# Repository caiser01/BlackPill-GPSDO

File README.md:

# BlackPill GPSDO
A custom PCB design for use with AndrewBCN's STM32-GPSDO project (https://github.com/AndrewBCN/STM32-GPSDO).

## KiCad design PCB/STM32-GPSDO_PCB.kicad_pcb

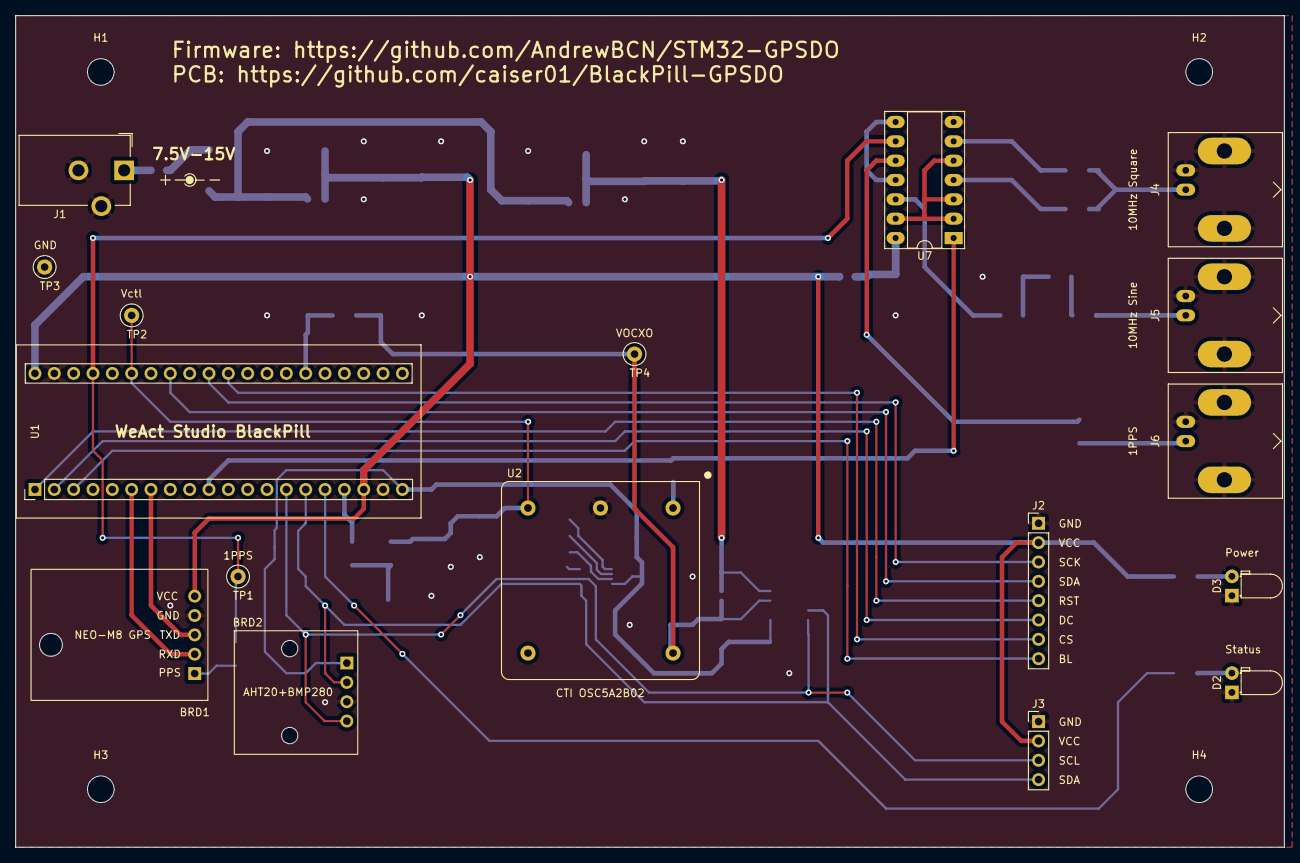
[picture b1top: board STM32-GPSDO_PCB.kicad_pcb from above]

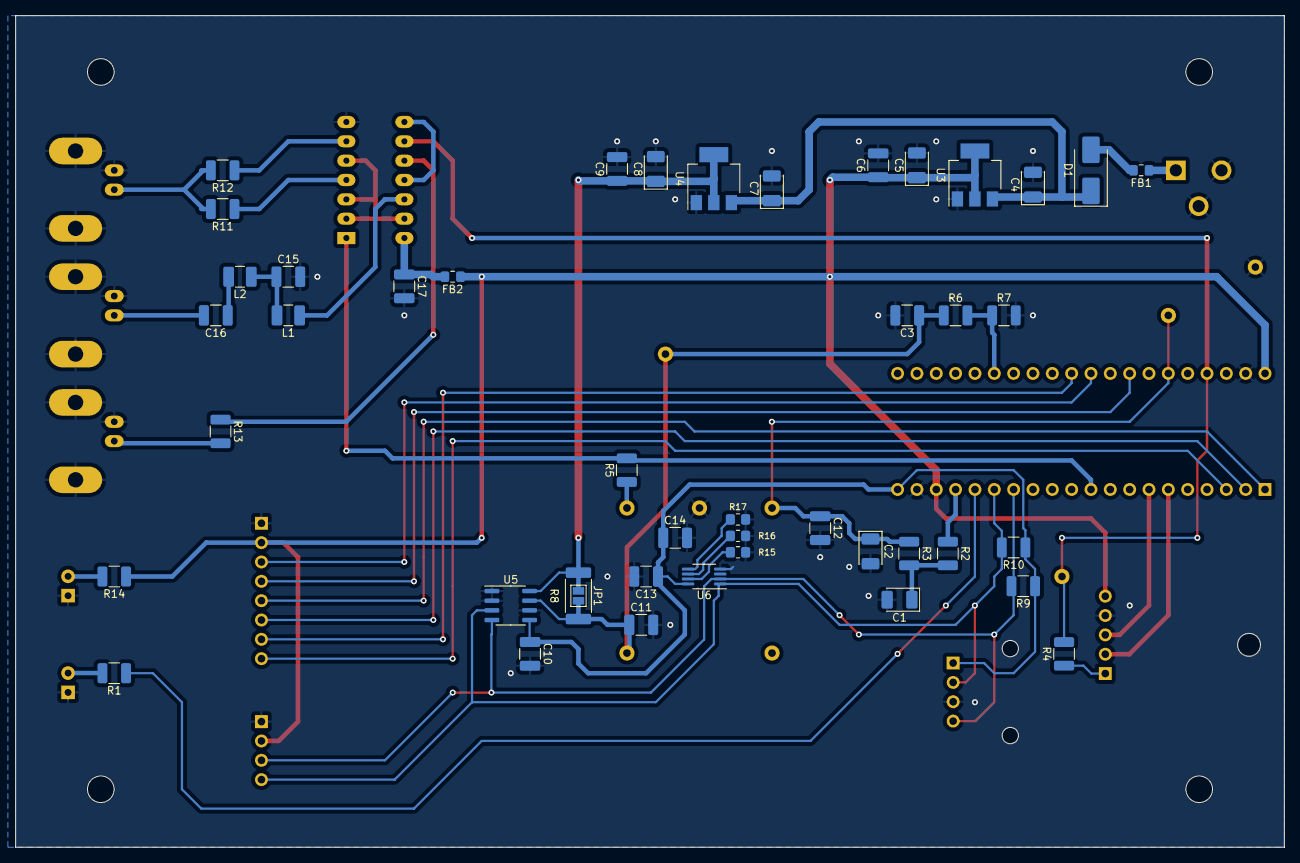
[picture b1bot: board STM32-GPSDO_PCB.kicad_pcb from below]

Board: 2 copper layers, 166.6 x 109.2 mm, 65 parts (44 on the bottom side), 44 nets.

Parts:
BRD1: NEO-M8N_GPS_Module; PCB_modules_GPS_NEO-M8N_PCB
BRD2: AHT20+BMP280_Module; PCB_modules_AHT20_BMP280_PCB
C1, C2: 10μF / 16V; CP_EIA-3528-15_AVX-H_Pad1.50x2.35mm_HandSolder
C3, C6, C9, C10, C11, C12, C13, C16, C17: 0.1μF; C_1210_3225Metric_Pad1.33x2.70mm_HandSolder
C4, C5, C7, C8: 10μF; CP_EIA-3528-12_Kemet-T_Pad1.50x2.35mm_HandSolder
C14: 10μF; C_1210_3225Metric_Pad1.33x2.70mm_HandSolder
C15: 47pF; C_1210_3225Metric_Pad1.33x2.70mm_HandSolder
D1: S2M-13-F; D_SMB_Handsoldering
D2: Status; LED_D3.0mm_Horizontal_O1.27mm_Z2.0mm
D3: Power; LED_D3.0mm_Horizontal_O1.27mm_Z2.0mm
FB1, FB2: MH2029-300Y; L_0805_2012Metric_Pad1.15x1.40mm_HandSolder
H1, H2, H3, H4: MountingHole; MountingHole_3.5mm
J1: Barrel_Jack_Switch; BarrelJack_CUI_PJ-102AH_Horizontal
J2: LCD_SPI; PinHeader_1x08_P2.54mm_Vertical
J3: LCD_I2C; PinHeader_1x04_P2.54mm_Vertical
J4, J5, J6: Conn_Coaxial; BNC_Amphenol_B6252HB-NPP3G-50_Horizontal
JP1: N.O.; SolderJumper-2_P1.3mm_Open_Pad1.0x1.5mm
L1, L2: L_Ferrite 10μH; L_1210_3225Metric_Pad1.42x2.65mm_HandSolder
R1: 330; R_1210_3225Metric_Pad1.30x2.65mm_HandSolder
R2, R3: 22k; R_1210_3225Metric_Pad1.30x2.65mm_HandSolder
R4, R11, R12: 100; R_1210_3225Metric_Pad1.30x2.65mm_HandSolder
R5: 180; R_1210_3225Metric_Pad1.30x2.65mm_HandSolder
R6, R7: 4.7k 1%; R_1210_3225Metric_Pad1.30x2.65mm_HandSolder
R8: 0.1/1% PT2512FK-070R1L; R_2512_6332Metric_Pad1.40x3.35mm_HandSolder
R9, R10: 10k; R_1210_3225Metric_Pad1.30x2.65mm_HandSolder
R13: 220; R_1210_3225Metric_Pad1.30x2.65mm_HandSolder
R14: 470; R_1210_3225Metric_Pad1.30x2.65mm_HandSolder
R15, R16, R17: 10k; R_0805_2012Metric_Pad1.20x1.40mm_HandSolder
TP1: 1PPS; TestPoint_Loop_D2.50mm_Drill1.0mm
TP2: Vctl; TestPoint_Loop_D2.50mm_Drill1.0mm
TP3: GND; TestPoint_Loop_D2.50mm_Drill1.0mm
TP4: VOCXO; TestPoint_Loop_D2.50mm_Drill1.0mm
U1: YAAJ_WeAct_BlackPill_Part_Like; YAAJ_WeAct_BlackPill_2
U2: OSC5A2B02; OCXO_CTI_OSC5A2B02
U3, U4: SPX1117M3-L-5-0/TR; SOT-223-3_TabPin2
U5: INA219AxD; SOIC-8_3.9x4.9mm_P1.27mm
U6: MCP9808_MSOP; MSOP-8_3x3mm_P0.65mm
U7: 74HC14; DIP-14_W7.62mm_Socket_LongPads

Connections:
1PPS: R4.2, TP1.1, U1.37 (PB10), U7.9
10MHz: R5.2, U1.10 (PA15), U7.1
GND: BRD1.4 (GND), BRD2.3 (GND), C1.2, C2.2, C3.2, C4.2, C5.2, C6.2, C7.2, C8.2, C9.2, C10.2, C11.2, C12.2, C13.2, C14.2, C15.2, C17.2, D2.1 (K), D3.1 (K), J1.2, J1.3, J2.1, J3.1, J4.2 (Ext), J5.2 (Ext), J6.2 (Ext), R7.2, R15.2, R16.2, R17.2, TP3.1, U1.19 (GND), U1.39 (GND), U2.2 (GND), U3.1 (GND), U4.1 (GND), U5.1 (A1), U5.2 (A0), U5.6 (GND), U6.4 (GND), U7.7 (GND)
LCD_BL: J2.8, U1.3 (PB14)
LCD_CS: J2.7, U1.30 (PA4)
LCD_DC: J2.6, U1.2 (PB13)
LCD_RST: J2.5, U1.1 (PB12)
MOSI: J2.4, U1.33 (PA7)
unnamed: BRD1.1 (PPS), R4.1
unnamed: BRD1.2 (RXD), U1.6 (PA9)
unnamed: BRD1.3 (TXD), U1.7 (PA10)
unnamed: C1.1, R2.2, R3.1
unnamed: C15.1, L1.2, L2.1
unnamed: C16.1, L2.2
unnamed: D1.2 (A), FB1.2
unnamed: C4.1, C7.1, D1.1 (K), U3.3 (VI), U4.3 (VI)
unnamed: D2.2 (A), R1.2
unnamed: D3.2 (A), R14.2
unnamed: FB1.1, J1.1
unnamed: J4.1 (In), R11.2, R12.2
unnamed: C16.2, J5.1 (In)
unnamed: J6.1 (In), R13.2
unnamed: C8.1, C9.1, JP1.2 (B), R8.1, U4.2 (VO), U5.8 (IN+)
unnamed: L1.1, U7.12
unnamed: R11.1, U7.4
unnamed: R12.1, U7.6
unnamed: R13.1, U7.10
unnamed: R6.2, R7.1, U1.26 (PA0)
unnamed: R1.1, U1.16 (PB8)
unnamed: R2.1, U1.17 (PB9)
unnamed: R5.1, U2.1 (10MHz_Out)
unnamed: R15.1, U6.7 (A0)
unnamed: R16.1, U6.6 (A1)
unnamed: R17.1, U6.5 (A2)
unnamed: U7.8, U7.11
unnamed: U7.2, U7.3, U7.5, U7.13
unnamed: C17.1, FB2.2, U7.14 (VCC)
SCK: J2.3, U1.31 (PA5)
SCL1: BRD2.4 (SCL), J3.3, R9.2, U1.14 (PB6), U5.4 (SCL), U6.2 (SCL)
SDA1: BRD2.2 (SDA), J3.4, R10.2, U1.15 (PB7), U5.3 (SDA), U6.1 (SDA)
VCC: BRD1.5 (VCC), C5.1, C6.1, FB2.1, J2.2, J3.2, R14.1, U1.18 (5V), U1.40 (5V), U3.2 (VO)
VDD: BRD2.1 (VDD), C10.1, C13.1, C14.1, R9.1, R10.1, U1.20 (3V3), U5.5 (VS), U6.8 (V_{DD})
VOCXO: C3.1, C11.1, JP1.1 (A), R6.1, R8.2, TP4.1, U2.5 (Vcc), U5.7 (IN-)
Vctl: C2.1, C12.1, R3.2, TP2.1, U1.35 (PB1), U2.3 (Vadj)

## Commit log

2024-01-16 Add KiCad PCB files and submodule for STM32-GPSDO firmware
